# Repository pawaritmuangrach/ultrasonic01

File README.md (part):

# Ultrasonic 40 kHz TDOA — จากต้นแบบ 1 TX + 2 RX สู่ Array แทน LiDAR

หลักการและที่มาของสูตรทั้งหมดอยู่ใน [`US015_TDOA_Codex_Spec.md`](US015_TDOA_Codex_Spec.md) เอกสารนี้สรุปเฉพาะสิ่งที่จำเป็นต่อการต่อวงจร รัน และตีความผลลัพธ์

หัวข้อ 1-6 คือต้นแบบเริ่มต้น (1 TX + 2 RX บน Arduino Nano) ที่ build/upload/ทดสอบจริงแล้ว — ถ้าต้องการภาพรวม
การออกแบบขั้นสูงขึ้น (Y-array, MIMO, ทำไม phased array ใช้ไม่ได้, เปรียบเทียบ Nano/ESP32) ข้ามไปหัวข้อ
**[7. จากต้นแบบ TDOA สู่การออกแบบ Ultrasonic Array เต็มรูปแบบ](#7-จากต้นแบบ-tdoa-สู่การออกแบบ-ultrasonic-array-เต็มรูปแบบ-y-array--mimo)** ได้เลย

## 1. Wiring

```
US-015 board 1 (มีตัวส่ง T และตัวรับ R1)
  VCC  -> 5V
  GND  -> GND
  TRIG -> Nano A2
  ECHO -> Nano A0

US-015 board 2 (ถอด/ปิดหัวส่ง ใช้เฉพาะตัวรับ R2)
  VCC  -> 5V
  GND  -> GND
  TRIG -> Nano A2   (สาย TRIG ต่อร่วมกับบอร์ด 1)
  ECHO -> Nano A1
```

A0/A1/A2 ถูกใช้เป็นขา **digital** ล้วน (PC0/PC1/PC2) ไม่มีการเรียก `analogRead()` กับ ECHO เพราะ ECHO เป็นสัญญาณ LOW/HIGH ไม่ใช่ waveform 40 kHz จริง

### 1.1 กรณีใช้ทรานสดิวเซอร์ดิบ (ไม่มี comparator ในตัว)

ถ้าฮาร์ดแวร์ของคุณเป็นทรานสดิวเซอร์ดิบต่อตรงเข้า A0/A1 (ไม่ใช่โมดูล US-015/HC-SR04 สำเร็จรูปที่มีวงจรขยาย+comparator ในตัว) **จะใช้งานไม่ได้** เพราะสัญญาณจาก piezo รับเป็น AC ระดับ mV เท่านั้น ขา digital input จะไม่เห็น echo จริง ต้องเพิ่มวงจร analog front-end ต่อหน้า A0/A1 แต่ละช่อง ประกอบด้วย 4 สเตจ (ทรานซิสเตอร์ NPN ทั่วไป 4 ตัว/ช่อง):

1. ขยายสัญญาณ 2 สเตจ (common-emitter amplifier, AC-coupled)
2. Envelope detector (ใช้ขา Base-Emitter ของทรานซิสเตอร์อีกตัวแทนไดโอด + ตัวเก็บประจุ)
3. Threshold switch (ทรานซิสเตอร์อีกตัวทำหน้าที่เทียบระดับแทน comparator IC)

วงจรนี้ **output จะ idle ที่ HIGH แล้วลง LOW เมื่อพบสัญญาณ** (กลับด้านกับโมดูลสำเร็จรูป) โค้ดมี flag `ECHO_ACTIVE_LOW` (ตั้งเป็น 1 ไว้แล้วในไฟล์ .ino) เพื่อรองรับ polarity แบบนี้ — ถ้าเปลี่ยนไปใช้โมดูลสำเร็จรูปจริงในอนาคต ให้ตั้งกลับเป็น 0

แนะนำจัดวางแบบสมมาตรสำหรับ calibrate:

```
R1        T        R2
|---------|---------|
      แผ่นสะท้อนเรียบ 30-50 cm ด้านหน้า
```

## 2. Flash และเปิด Serial

1. เปิด `ultrasonic_tdoa_nano/ultrasonic_tdoa_nano.ino` ด้วย Arduino IDE, เลือกบอร์ด "Arduino Nano" / processor ATmega328P (เก่า ถ้า upload ไม่ผ่านให้ลอง "ATmega328P (Old Bootloader)")
2. Upload
3. เปิด Serial Monitor/Serial Plotter ที่ **115200 baud** — หรือใช้หน้าเว็บ simulation ใน `simulation/index.html` แทน (ดูหัวข้อ 6)

ค่าเริ่มต้นของ output คือ **CSV** (ส่ง `s` ทาง Serial เพื่อสลับเป็น human-readable)

Header ของ CSV:

```
timestamp_ms,r1_pulse_us,r2_pulse_us,r1_cm,r2_cm,raw_dt_us,calibrated_dt_us,path_diff_cm,angle_deg,confidence,status,cycle_shift
```

ตัวอย่างบรรทัดข้อมูล:

```
1250,212.5,230.5,3.64,3.95,18.0,18.0,0.617,7.10,91,VALID,0
```

Human-readable (หลังส่ง `s`):

```
R1=212.5us 3.64cm | R2=230.5us 3.95cm | raw_dt=18.0us | calibrated_dt=18.0us | path=0.617cm | angle=7.10deg | confidence=91 | status=VALID | cycle_shift=0
```

## 3. Serial Commands

| คำสั่ง | ผลลัพธ์ |
|---|---|
| `c` | เริ่ม calibration (เก็บ ~200 samples แล้วหา median offset ของ raw dt) — **ต้องวางอุปกรณ์สมมาตรตามรูปด้านบนก่อนส่งคำสั่งนี้** |
| `p` | พิมพ์ parameters ปัจจุบัน (sound speed, spacing, offset, output mode) |
| `r` | ล้าง median-filter / cycle-slip history |
| `s` | สลับ CSV <-> human-readable |
| `t25` | ตั้งอุณหภูมิ 25 °C แล้วคำนวณความเร็วเสียงใหม่ |
| `d5.0` | ตั้ง receiver spacing เป็น 5.0 cm |

## 4. สมการหลัก

```
pulse_us          = fall_tick - rise_tick   (Timer1, 0.5 us/tick)
distance_cm       = pulse_us * c / 2                      (ระยะแบบ pulse-echo ปกติ)
raw_dt_us         = pulse2_us - pulse1_us
calibrated_dt_us  = raw_dt_us - calibration_offset_us      (+ cycle-slip correction)
path_diff_cm      = calibrated_dt_us * c                   (ไม่หาร 2 เพราะเทียบเส้นทางถึงตัวรับสองตัว)
max_dt_us         = receiver_spacing_cm / c                 (ขอบเขตทางฟิสิกส์)
angle_deg         = asin(path_diff_cm / receiver_spacing_cm) * 180/pi   (เฉพาะเมื่อ status == VALID)
```

`c = 0.0343 cm/us` ที่อุณหภูมิห้อง (ปรับได้ด้วยคำสั่ง `t<celsius>`)

## 5. ข้อจำกัดสำคัญ (อ่านก่อนเชื่อผลลัพธ์)

1. US-015 เป็น black-box — ECHO ที่เห็นคือผลหลัง comparator/threshold ภายในโมดูล ไม่ใช่ raw 40 kHz waveform
2. `raw_dt_us` **ไม่รับประกัน** ว่าเท่ากับส่วนต่างเวลาที่คลื่นมาถึงจริง เพราะแต่ละบอร์ดมี internal delay/threshold ไม่เท่ากัน — ต้อง calibrate (`c`) ก่อนเสมอ
3. Calibration ลบ static offset ได้ แต่ลบ dynamic jitter ไม่ได้ทั้งหมด
4. `cycle_shift != 0` แปลว่าเกิด cycle-slip correction (ค่ากระโดดเป็นทวีคูณของ 25 us) — เป็น heuristic ไม่ใช่การพิสูจน์
5. `angle_deg` ใช้สมมติฐาน far-field / plane-wave ถ้าวัตถุอยู่ใกล้มาก มุมนี้จะไม่แม่น
6. ผลลัพธ์ทั้งหมดควรเรียกว่า **pseudo-TDOA** ไม่ใช่ true TDOA จนกว่าจะเข้าถึง raw receiver signal ได้จริง (ดูหัวข้อ 27 ในสเปก)
7. ไม่ควรใช้ระบบนี้ในงาน safety-critical

## 6. Real-time 2D wave simulation

`simulation/index.html` เป็นหน้าเว็บ (self-contained, ไม่ต้องติดตั้งอะไร) ที่:

- ต่อกับ Arduino ผ่าน **Web Serial API** (Chrome/Edge เท่านั้น) ที่ 115200 baud
- อ่านบรรทัด CSV ทีละแถว แล้ววาดภาพ 2D: ตำแหน่ง T/R1/R2, คลื่นวงกลมที่ขยายตัวออกจาก T ไปกระทบวัตถุ (คำนวณตำแหน่งวัตถุจาก r1_cm และระยะ target->R2 ที่แปลงจาก r2_pulse_us) แล้วมีคลื่นสะท้อนกลับไปหา R1 และ R2 พร้อม timing สัมพัทธ์ตามข้อมูลจริง (สโลว์โมชันเพื่อให้ตามองเห็น)
- มีปุ่ม **Demo mode** สำหรับดูตัวอย่างการทำงานโดยไม่ต้องต่อ Arduino จริง
- **สะสมจุดสะท้อนทุกจุดที่ตรวจพบ** (ไม่ใช่แค่ ping ล่าสุด) เป็นแผนที่จุดสีชมพูบานเย็น (magenta point cloud) คล้าย
  scatter plot ของ SLAM map — จุดที่วัดได้ต่อเนื่องกันและอยู่ใกล้กัน (<15 cm) จะมีเส้นเชื่อมให้ดูเป็นขอบวัตถุ/กำแพงคร่าวๆ
  เอาเมาส์ชี้จุดใดก็ได้เพื่อดูระยะ/มุม/confidence ของจุดนั้น มีปุ่ม "Clear Map" และ "Export Map (CSV)"
  หมายเหตุ: เซนเซอร์ชุดนี้ไม่ได้หมุนสแกนแบบ lidar การจะได้แผนที่ห้องเต็มรูปแบบต้องเลื่อน/หมุนวัตถุหรือตัวเซนเซอร์เอง
  แล้วเก็บผลสะสมไว้ (เหมาะกับ Experiment 4 ในสเปก)

วิธีใช้:

1. อัปโหลดโค้ดลง Arduino Nano และปิด Serial Monitor ใน Arduino IDE ก่อน (พอร์ตใช้ได้ทีละโปรแกรม)
2. เปิด `simulation/index.html` ด้วย **Chrome หรือ Edge** (ดับเบิลคลิกเปิดไฟล์ได้เลย ไม่ต้องมี server)
3. กดปุ่ม "Connect Arduino" แล้วเลือกพอร์ต COM ของ Nano
4. ดูคลื่นวิ่งแบบ real-time ทุกครั้งที่ Arduino ยิงคลื่นออกไป

ถ้าต้องการดูตัวอย่างก่อนต่อฮาร์ดแวร์จริง ให้กด "Demo mode (no hardware)" แทน

---

## 7. จากต้นแบบ TDOA สู่การออกแบบ Ultrasonic Array เต็มรูปแบบ (Y-array + MIMO)

หัวข้อ 1-6 ด้านบนคือต้นแบบเริ่มต้น (1 TX + 2 RX, US-015/front-end แบบ discrete transistor) ต่อมาโปรเจกต์ขยายเป้าหมาย
เป็น **ใช้ ultrasonic array แทน LiDAR** สำหรับ obstacle avoidance ระยะใกล้ (เทรน NN โดยใช้กล้องเป็น ground truth)
หัวข้อนี้สรุปข้อค้นพบและการออกแบบที่ได้จากการสำรวจแนวทางต่างๆ

### 7.1 ทำไมตัวส่งหลายตัว + ตัวรับตัวเดียว (phased array) ใช้ไม่ได้

แนวคิดแรกที่พิจารณาคือใช้ตัวส่งหลายตัวรวมคลื่นเป็นลำแคบแล้วกวาดทิศทาง (transmit beam steering) แต่พบข้อจำกัดทาง
ฟิสิกส์ที่แก้ไม่ได้:

- ที่ 40kHz, c=343 m/s → ความยาวคลื่น **λ ≈ 8.575mm** → ต้องวางตัวส่งห่างกันไม่เกิน **λ/2 ≈ 4.3mm** ถึงจะไม่เกิด
  ลำคลื่นหลอก (grating lobe)
- ทรานสดิวเซอร์ TCT40-16 มีตัวถังจริง **16mm** — ใหญ่กว่าที่ต้องการเกือบ 4 เท่า และไม่มีทางวางให้ใกล้กว่านี้ได้
  เพราะเป็นขนาดจริงของอุปกรณ์ในอากาศ
- ทดสอบด้วยการจำลอง (`simulation/beamforming_compare.html`) ยืนยันว่าที่ระยะ 16mm ยิงพร้อมกันเกิดลำคลื่นแรง
  พร้อมกัน **3 ทิศ** (-32°, 0°, 32°) และถ้าพยายาม steer ไป 20° ด้วยการหน่วงเวลา จะยิ่งแย่ลงเป็น **4 ทิศ**
  (-47°, -11°, 20°, 61°)
- **ปัญหานี้แก้ด้วยซอฟต์แวร์ไม่ได้เลย** เพราะพลังงานเสียงกระจายผิดทิศไปแล้วตั้งแต่ในอากาศ ไม่ใช่ความผิดพลาดของ
  การประมวลผลสัญญาณ

สรุป: ตัวส่งหลายตัวยิงพร้อมกันเพื่อเล็งลำคลื่นไม่ใช่ทางที่ไปได้กับทรานสดิวเซอร์ขนาดนี้

### 7.2 ทางที่เลือกแทน: TDOA (วัดเวลา ไม่ใช่วัดเฟส)

แทนที่จะเล็งลำคลื่นตอนส่ง เปลี่ยนมายิงคลื่นกระจายกว้างครั้งเดียว แล้วใช้ **ตัวรับหลายตัว** ฟังพร้อมกัน คำนวณทิศทาง
จากผลต่างเวลาที่เสียงมาถึงแต่ละตัว (`sinθ = c·Δt/d`) สมการนี้มีคำตอบเดียวเสมอ (วัดเวลา ไม่ใช่เฟสที่วนซ้ำทุกคาบ)
จึง**ไม่มี grating lobe** — เป็นเหตุผลที่ต้นแบบในหัวข้อ 1-6 ใช้สถาปัตยกรรมนี้มาตั้งแต่แรก

กฎของ aperture ก็กลับด้านจาก phased array: ความละเอียดเชิงมุม `θ_res ≈ λ/D` → **ยิ่งตัวรับกระจายกว้าง (D ใหญ่)
ยิ่งแยกมุมได้ละเอียด** ตรงข้ามกับ phased array ที่ต้องการให้ชิดกัน

### 7.3 ขยายเพิ่มด้วย MIMO (coded TX หลายตัว)

ยิงตัวส่งหลายตัว**พร้อมกัน**โดยแต่ละตัวใช้ code ต่างกัน (แยกด้วย matched filter ฝั่งรับ) จะได้เส้นทางข้อมูล
(TX→วัตถุ→RX) แยกกันได้ = จำนวน TX × จำนวน RX (virtual array, ตำแหน่งเสมือน = ตำแหน่ง TXi + RXj) — ได้ข้อมูล
เพิ่มแบบ**ทวีคูณ**จากอุปกรณ์ที่เพิ่มแบบบวก และยังยิงครั้งเดียวจบเหมือนเดิม (ไม่ช้าลง เพราะยิงพร้อมกัน) ต่างจาก
การยิงตัวส่งทีละตัว (reciprocity ให้ข้อมูลเท่ากันแต่ช้ากว่า 6 เท่าและวงจรซับซ้อนกว่า จึงไม่คุ้ม)

### 7.4 ผังที่แนะนำ: Scaled Array — 3 TX + 9 RX (12 อุปกรณ์จริง, 27 เส้นทางเสมือน)

- **TX1-TX3**: กลุ่มสามเหลี่ยมเล็กกึ่งกลางแผง (รัศมี 14mm จากศูนย์กลาง — ห่างพอให้ตัวถัง 16mm ไม่ชนกัน)
- **RX1-RX9**: 3 แขนมุม 120° (แบบเดียวกับผัง VLA radio telescope เพื่อ sampling มุมสม่ำเสมอทุกทิศ) แขนละ 3 ตัว
  ที่ระยะ **40 / 80 / 140mm** (140mm คือตัวขยายใหม่จากเดิม 40/80mm)
- แต่ละแขนให้ทั้งข้อมูล azimuth (ซ้าย-ขวา) และ elevation (บน-ล่าง) พร้อมกัน
- Diminishing returns: ขยายรัศมี 40→60mm ได้ θ_res ดีขึ้น 2.05° แต่ขยาย 140→160mm ได้แค่ 0.22° (จึงหยุดที่ 140mm)
- Circuit BOM เต็มระบบ: TX driver (TC4427A) 3 ชุด, MCP6024 (quad op-amp, 2 RX/ชิป) 5 ชิป, วงจร VREF 2.5V 1 ชุด
  (ใช้ร่วมกันได้ทุกช่อง)

### 7.5 ข้อจำกัดของแพลตฟอร์มควบคุม (Nano / ESP32 / ESP32+ADS1115)

| แพลตฟอร์ม | RX สูงสุดที่ใส่ได้จริง | จับ raw chirp 40kHz ได้ไหม | MIMO coded TX |
|---|---|---|---|
| Arduino Nano | ≤6-7 (จาก 8 ขา A0-A7) | ไม่ได้ (ADC มัลติเพล็กซ์ช้าเกิน) → ใช้ envelope+threshold แทน | ไม่ไหว |
| ESP32 เดี่ยว | 8 (ADC1) | ได้ (DMA ~100-500kS/s) | ได้ 3 ตัวเต็มรูปแบบ |
| ESP32 + ADS1115 | 8 + 4 (I2C) | เฉพาะช่อง ESP32; ADS1115 ช้าเกิน (860 SPS) ใช้ได้แค่ envelope | ได้ 3 ตัว |

**สรุป**: ผัง 3TX+9RX เต็มรูปแบบต้องใช้ ESP32+ADS1115 แบบ hybrid (RX 8 ช่องแรกจับ raw waveform ผ่าน ESP32,
RX "far" 140mm ที่เหลือจับแค่ envelope ผ่าน ADS1115) — Nano ทำได้แค่ 1TX+6RX แบบ envelope เท่านั้น

### 7.6 เครื่องมือ visualization ทั้งหมด (self-contained, เปิดตรงจากไฟล์ได้)

| ไฟล์ | ใช้ทำอะไร |
|---|---|
| `simulation/index.html` | Real-time 2D wave + point-cloud map จากข้อมูล serial จริง (หัวข้อ 6) |
| `simulation/beamforming_compare.html` | เปรียบเทียบ interference pattern 2-TX ที่ระยะห่างต่างกัน (λ/2 vs 16mm vs steered) — ที่มาของข้อสรุปข้อ 7.1 |
| `simulation/sparse_array_layout.html` | ผัง L-shape sparse receiver บนโต๊ะ (สำหรับทดลองเก็บข้อมูล + กล้องเป็น ground truth) |
| `simulation/front_array_plate_layout.html` | ผังหน้าแผง Y-array รุ่นแรก (1 TX + 6 RX) พร้อม difference co-array |
| `simulation/mimo_virtual_array_layout.html` | สาธิต MIMO virtual array (3 TX + 4 RX ตัวอย่าง) เทียบกับผัง 1TX+6RX |
| `simulation/scaled_array_layout.html` | ผังสุดท้าย 3TX+9RX เต็มรูปแบบ + diminishing returns + เทียบ 3 แพลตฟอร์ม (7.4-7.5) |
| `diagnostics/r1_basic_test/r1_basic_test.ino` | สเก็ตช์ทดสอบเปล่า (`pulseIn()`) ใช้แยกว่าปัญหา R1 ค้างที่ 4.6cm เป็นที่ฮาร์ดแวร์ ไม่ใช่เฟิร์มแวร์ |

### 7.7 ข้อจำกัดที่ยังเหลืออยู่

**Cycle slip**: คลื่น 40kHz คาบ 25µs ถ้าวัดเวลาไม่แม่นพอ ระบบอาจสับสนว่าจับคลื่นลูกไหน (ค่ากระโดดเป็นก้อนละ ~25µs
— ปรากฏการณ์เดียวกับที่เจอจริงตอน calibrate ฮาร์ดแวร์ในหัวข้อ 2-3) ต่างจาก grating lobe ตรงที่**แก้ได้** ด้วย:

1. Chirp + Pulse Compression (แผนระยะยาว) — กวาดความถี่แทนโทนเดียว ทำให้วัดเวลาคมขึ้นมาก
2. วางตัวรับแบบ sparse/non-redundant — ความกำกวมของแต่ละคู่ตกคนละมุม ไม่ทับกัน
3. Neural Network + กล้องเป็น ground truth — เรียนรู้ล้างส่วนที่เหลือจากข้อมูลจริง

**ข้อจำกัดที่ต้องยอมรับ**: อัลตราโซนิกในอากาศไม่มีวันเทียบ LiDAR ได้ในเรื่องระยะไกล (สิบ-ร้อยเมตร) และความละเอียด
ระดับ mm — เป้าหมายที่สมจริงคือใช้แทนได้เฉพาะบริบท obstacle avoidance ระยะใกล้ (<5-10m) เท่านั้น

---

## 8. ESP32 build log — Stage 1

บันทึกสิ่งที่**วัดได้จริง**บนฮาร์ดแวร์ ไม่ใช่ค่าออกแบบ ทุกตัวเลขในหัวข้อนี้มาจากการวัดด้วย
`esp32_selftest.ino` + `tools/scope_view.py` บนบอร์ด ESP32-D0WD-V3 rev 301 ที่ COM5

### 8.1 สถานะ

| งาน | สถานะ |
|---|---|
| เครื่องมือ (arduino-cli, Python, scope_view) | ✅ |
| พิสูจน์ ADC ต่อเนื่อง 2 MS/s | ✅ |
| ภาคส่ง TX driver Version A | ✅ |
| **ภาครับ RX front-end 1 ช่อง** | ✅ |
| `esp32_scope.ino` (ยิง burst + เก็บคลื่น) | ✅ |
| เห็น echo หลายก้อนในหนึ่งช็อต | ✅ |
| ระยะเลื่อนตาม `t = 2d/c` เมื่อขยับแผ่นสะท้อน | ⬜ |

### 8.2 ADC ต่อเนื่อง — สมมติฐานที่เสี่ยงที่สุดของโปรเจกต์

ทั้งโครงการตั้งอยู่บนข้อสมมติว่า ESP32 สตรีม ADC1 ได้ระดับ MS/s ผลจริง:

| ขอ | ได้จริง | % |
|---|---|---|
| 1,000,000 S/s | 976,400 | 97.6% |
| 1,500,000 S/s | 1,464,200 | 97.6% |
| 2,000,000 S/s | 1,951,900 | 97.6% |

เปอร์เซ็นต์คงที่ทั้งสามค่า แปลว่าเป็น**ค่าโสหุ้ยคงที่ ไม่ใช่เพดาน** — แผน Stage 3
(6 ช่อง × 325 kS/s) จึงใช้ได้จริง

### 8.3 RX front-end — ผลวัดหลังแก้จนนิ่ง

โครงสร้าง: `TCT40-16R → Cin 100nF → 2 สเตจ non-inverting เกน 10.3/สเตจ → R 2.2k + C 1nF → GPIO34`
ไฟเลี้ยง 3.3V, VREF 1.65V จากตัวแบ่ง 10k/10k + บัฟเฟอร์

| ตัวชี้วัด | ค่าที่วัดได้ |
|---|---|
| จุดปฏิบัติการ DC ที่ขาออก | 1.521-1.523 V นิ่งทุกเฟรม |
| ฮัม 50 Hz ที่ขาออก | 3.5 mV |
| พื้นเสียงรบกวน 30-50 kHz | 3.2 mV ที่ขาออก = **30 µV ที่ขาเข้า** |
| จุดอิ่มตัว | 1167 mV rms = 11 mV ที่ขาเข้า |
| ช่วงไดนามิก | **51 dB** |
| ตัวอย่างที่ชนราง (16,000 ตัวอย่าง) | 0 |

> DC 1.52 V ไม่ใช่ความผิดพลาด — ADC ของ ESP32 อ่านต่ำกว่าจริงราว 7% ที่ช่วงกลางสเกล
> `1.65 × 0.923 = 1.523` ตรงกับที่วัดได้ ต้องคาลิเบรตก่อนใช้ค่าสัมบูรณ์

**ทดสอบตอบสนองอัลตราโซนิก** (เขย่าพวงกุญแจห่าง ~10 cm):

| | พลังงานย่าน 30-50 kHz |
|---|---|
| ห้องเงียบ | 3.2 mV |
| เขย่ากุญแจ | 337.4 mV (**105 เท่า**) |

หลักฐานที่หนักแน่นกว่าความแรงคือ**ความถี่**: กุญแจให้เสียงกว้าง แต่ยอดที่จับได้ทุกเฟรมตกอยู่ที่
36.07 / 37.31 / 37.33 / 37.35 / 38.00 / 38.04 / 38.07 / 40.70 kHz — เกาะกลุ่มในย่านเรโซแนนซ์
ของ TCT40 ทั้งหมด ถ้าเป็นเพียงสัญญาณรบกวน ยอดจะกระจายแบบสุ่มทั่วย่าน

### 8.4 ปัญหาที่เจอจริงและวิธีวินิจฉัย

บันทึกไว้เพราะทั้งสี่ข้อจะกลับมาอีกตอนขยายเป็น 6 ช่อง

| อาการ | สาเหตุจริง | วิธีที่ชี้ตัวได้ |
|---|---|---|
| ขาออกแกว่งเต็มราง 3.3 Vpp ที่ 50 Hz | **รางไฟบนบอร์ดทดลองถูกตัดขาดกลางแผ่น** ครึ่งล่าง (ตัวแบ่ง VREF, C 10µF, Cg, C_out, คาปาบายพาส) ไม่มีทั้งไฟและกราวด์ กลายเป็นเสาอากาศรับไฟบ้าน แล้ว C 10µF ป้อนเข้า VREF ตรงๆ | ย้ายสายวัดไปที่รางกราวด์เอง — อ่านได้ 0.556 V แกว่ง 3.3 Vpp ซึ่งเป็นไปไม่ได้ถ้าต่อถึงกราวด์จริง |
| แยกไม่ออกว่าวงจรเสียหรือสายวัดลอย | — | อ่านขาที่**ไม่ได้ต่ออะไรเลย** (GPIO36/39) เทียบ ได้ 22 mV เทียบกับ 2093 mV จึงยืนยันว่าวงจรสร้างสัญญาณจริง |
| ไม่รู้ว่าเป็นการแกว่งเองหรือรับจากภายนอก | ฮัมจากภายนอก | ดูค่าดิบ: 98.5% ของตัวอย่างเป็น 0 หรือ 4095 เป๊ะ ฮาร์มอนิก 49/146/244/342 Hz อัตราส่วน 1 : ⅓ : ⅕ : ⅐ = คลื่นสี่เหลี่ยมที่ถูกตัดยอด ไม่ใช่การแกว่งของ op-amp |
| ออปแอมป์ตัวที่ 4 ที่ไม่ได้ใช้ | ขา 12 (ขาออก) ต่อลงกราวด์ = ลัดวงจร ส่วนขา 13/14 ลอย | อินพุต CMOS ที่ลอยจะทำตัวเป็นตัวเปรียบเทียบรับไฟบ้าน — **ออปแอมป์ที่ไม่ได้ใช้ต้องต่อเป็นวงจรตามแรงดัน**: ขาออก↔อินพุต− และอินพุต+ ลงกราวด์ |

**บทเรียนที่ใช้ซ้ำได้**: ตอนที่ `Cg` เปลี่ยนเป็น 1nF เกนที่ 50 Hz เหลือ 1.03/สเตจ ทำให้ขาออกของ
สเตจ 1 กับสเตจ 2 ให้ค่า**เท่ากันเป๊ะทุกหลัก** (2093.5 กับ 2093.7 mV) ทั้งที่สเตจ 2 ควรขยาย
สเตจ 1 อีก 10 เท่า — ความผิดปกตินี้เองที่ชี้ว่าปัญหาอยู่**เหนือ**ทางขยายขึ้นไป คือที่ VREF
การเปลี่ยนอะไหล่ครั้งนั้นไม่ได้แค่แก้ฮัม แต่เปลี่ยนวงจรให้กลายเป็นเครื่องมือวินิจฉัยด้วย

### 8.5 คำสั่งที่ใช้วัดซ้ำได้

```bash
python tools/scope_view.py --port COM5 --dc --probe 34 --rate 200000 --samples 8000
```

### 8.6 ผลยิงจริงครั้งแรก — ภาคส่ง + ภาครับ ครบวงจร

เฟิร์มแวร์ `esp32_array/esp32_scope/esp32_scope.ino` ยิง burst 8 รอบที่ 40 kHz ออก GPIO25
แล้วเก็บคลื่นจาก GPIO34 ที่ 500 kS/s หน้าต่าง 48 ms (= ระยะ 8.2 m)

**หนึ่งช็อตเห็นวัตถุ 8 ก้อน** (แปลงเป็นระยะจากผลต่างกับพัลส์ตรง):

| t (ms) | ห่างจากพัลส์ตรง | ระยะ | ยอด |
|---|---|---|---|
| 1.436 | — | พัลส์ตรง (t=0) | 49.0 mV |
| 3.789 | 2.352 ms | 40.3 cm | 74.3 mV |
| 4.394 | 2.957 ms | 50.7 cm | 26.0 mV |
| 6.155 | 4.718 ms | 80.9 cm | 81.9 mV |
| 7.709 | 6.273 ms | 107.6 cm | 35.8 mV |
| 8.300 | 6.864 ms | 117.7 cm | 41.9 mV |
| 8.925 | 7.489 ms | 128.4 cm | 29.3 mV |

**ความถี่พาหะที่วัดได้** (พารามิเตอร์บิน 61 Hz จากการประมาณค่าพาราโบลา): พัลส์ตรง 40.94 kHz,
เอคโค่ 41.03 / 41.83 kHz — อยู่ในกรอบ 40 ±1 kHz ตามเกณฑ์ และบอกด้วยว่า**เรโซแนนซ์จริงของคู่
ทรานสดิวเซอร์นี้อยู่ที่ ~41 kHz ไม่ใช่ 40 kHz พอดี** ลองสั่ง `s 41000` ดูอาจได้แรงขึ้นฟรีๆ

**SNR ของเอคโค่ที่ 40 cm = 29.5 dB** (พื้นหลัง 2.82 mV) เกณฑ์ Stage 1 ต้องการ ≥10 dB ที่ 50 cm

### 8.7 ทำไม t = 0 ต้องอ่านจากพัลส์ตรง ไม่ใช่จากเวลาที่ซอฟต์แวร์สั่งยิง

ยิงซ้ำ 8 ครั้งติดกัน วัดเวลามาถึงของพัลส์ตรง (ระยะทางคงที่ ไม่ควรขยับเลย):

| | ค่า |
|---|---|
| ตำแหน่งที่เฟิร์มแวร์ตั้งใจให้ยิง (`p 200`) | 0.200 ms |
| ตำแหน่งจริงเฉลี่ย | **1.454 ms** |
| ความคลาดเคลื่อนคงที่ | **1.25 ms = ระยะผิด 21 cm** |
| การกระจายรอบค่าเฉลี่ย | 24.3 µs (ช่วง 74 µs) |

ความคลาดเคลื่อนคงที่ 1.25 ms เกิดจาก DMA ของ ADC วิ่งอิสระ — ตอนที่เฟิร์มแวร์ล้างบัฟเฟอร์แล้ว
เริ่มนับ ตัวอย่างแรกที่ได้จริงไม่ได้เกิดขึ้น ณ วินาทีนั้น **ถ้าเชื่อเวลาของซอฟต์แวร์ ทุกระยะจะเพี้ยนไป
21 cm** แต่พอวัดเทียบกับพัลส์ตรงในข้อมูลเอง ความคลาดเคลื่อนนี้หักล้างหมดเกลี้ยง เพราะมันเข้าไป
อยู่ในทั้งสองพจน์เท่ากัน

วัดระยะซ้ำ 8 ครั้งกับวัตถุเดียวกันได้ **40.6 cm ± 7.3 mm**

> ข้อสังเกตที่สำคัญต่อ Stage 2: การกระจายของ**ผลต่าง** (42.4 µs) แย่กว่าการกระจายของ
> **เวลาสัมบูรณ์ของเอคโค่** (37.5 µs) ทั้งที่การลบควรหักสิ่งที่ร่วมกันออก แปลว่าตัวจำกัดความแม่น
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
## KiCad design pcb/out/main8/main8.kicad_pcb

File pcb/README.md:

# pcb — ข้อมูลและลายสำหรับสั่งทำ PCB

ทั้ง TX และ RX สร้างจากวงจรที่ **ต่อบนแผ่นไข่ปลาแล้วใช้งานได้จริง**
ไม่ได้ออกแบบวงจรใหม่ ที่มา: [`../hardware/rx_frontend.md`](../hardware/rx_frontend.md) ·
[`../hardware/tx_driver.md`](../hardware/tx_driver.md) และผังไข่ปลาใน `../hardware/diagrams/`

```bash
python pcb/build.py       # สร้างไฟล์ทั้งหมดใหม่
python pcb/check_out.py   # ตรวจไฟล์ที่จะส่งโรงงาน
```

---

## บอร์ดทั้งสาม

| บอร์ด | ขนาด | ทำอะไร | สั่งกี่แผ่น |
|---|---|---|---|
| **`tx3`** | 66.8 × 38.3 mm | ภาคส่ง 3 หัว จาก 74HCT04 ตัวเดียว | 1 |
| **`rx2`** | 86.8 × 73.8 mm | ภาครับ 2 ช่อง จาก MCP6004 ตัวเดียว | **5** (ได้ 10 ช่อง ใช้ 9) |
| **`vref`** | 68.8 × 51.9 mm | สร้าง 1.65V ครั้งเดียว แจกทุกบอร์ด | 1 |

### ทำไมแยก VREF ออกมาเป็นบอร์ดที่สาม

MCP6004 มี 4 section พอดีกับ 2 ช่องรับ (ช่องละ 2 สเตจ) **ไม่เหลือให้ทำบัฟเฟอร์ VREF**
ผังไข่ปลาเดิมแก้ด้วยการให้ชิปแรกทำแค่ 1 ช่อง แล้วเอา section ที่เหลือไปทำ VREF
ซึ่งทำให้บอร์ดสองแบบไม่เหมือนกัน สั่งทำแล้วยุ่ง

แยกออกมาได้บอร์ดรับที่ **เหมือนกันทุกแผ่น ปั๊มซ้ำได้** และได้ผลพลอยได้ที่สำคัญกว่า:
VREF เป็นจุดเดียวกันจริงทั้งระบบ ถ้าแต่ละบอร์ดสร้างเอง ค่าจะต่างกันตามความคลาด
ของตัวต้านทาน แล้วช่องต่าง ๆ จะมีจุดศูนย์ไม่ตรงกัน — เวลาเทียบความแรงระหว่างช่อง
(ซึ่งคือที่มาของมุม) จะเพี้ยน

---

## ไฟล์ในแต่ละโฟลเดอร์ `out/<บอร์ด>/`

| ไฟล์ | คืออะไร |
|---|---|
| `*-F_Cu.gbr` `*-B_Cu.gbr` | ลายทองแดงด้านบน / ด้านล่าง |
| `*-F_Mask.gbr` `*-B_Mask.gbr` | หน้ากากประสาน (เปิดเฉพาะตรงแป้น) |
| `*-F_Silkscreen.gbr` | ตัวหนังสือและกรอบชิ้นส่วนด้านบน |
| `*-Edge_Cuts.gbr` | เส้นตัดขอบบอร์ด |
| `*.drl` | ตำแหน่งและขนาดรูเจาะ |
| `preview.png` | ภาพตรวจด้วยตา — ม่วง/เขียวเข้ม = แผ่นกราวด์ · เขียวสด = ลายด้านล่าง |
| `assembly.png` | **ผังลงชิ้นส่วน ถือไว้ตอนบัดกรี** |
| `BOM.md` | รายการชิ้นส่วนของบอร์ดนั้น |
| `nets.md` | ตารางว่าขาไหนต้องปี๊บถึงขาไหน ไว้ไล่วัดด้วยมิเตอร์ |

---

## สั่งทำยังไง

zip ไฟล์ `.gbr` กับ `.drl` ของบอร์ดหนึ่งรวมกัน แล้วอัปโหลดที่ JLCPCB / PCBWay / Elecrow

ตั้งค่า: **2 ชั้น · หนา 1.6 mm · ทองแดง 1 oz** — ค่าเริ่มต้นของทุกเจ้าใช้ได้หมด
ไม่มีอะไรพิเศษ ราคาปกติ 5 แผ่นแรกไม่กี่สิบบาท

**ก่อนจ่ายเงิน ให้เปิดดูในตัวดู Gerber ของเว็บนั้นก่อนเสมอ** แล้วเทียบกับ `preview.png`
ถ้าสองภาพไม่เหมือนกัน อย่าสั่ง

### กติกาที่ใช้ออกแบบ (เผื่อไว้เยอะกว่าที่โรงงานทำได้)

| | ค่าที่ใช้ | โรงงานทั่วไปทำได้ |
|---|---|---|
| ลายสัญญาณ | 0.4 mm | 0.13 mm |
| ลายไฟ | 0.8 mm | |
| ระยะห่างขั้นต่ำ | 0.4 mm | 0.13 mm |
| รูเล็กสุด | 0.9 mm | 0.3 mm |
| ทองแดงรอบรู | 0.4 mm | 0.13 mm |

เผื่อเยอะขนาดนี้เพราะสองเหตุผล: สั่งเจ้าไหนก็ผ่านแน่ และถ้าจะกัดเองที่บ้านก็ยังทำได้

---

## ถ้าจะทำเอง (รีดลายลงแผ่นทองแดง)

`tx3` และ `vref` เดินลายอยู่ **ด้านล่างล้วน** (ลายด้านบน 0 เส้น) ทำหน้าเดียวได้เลย
`rx2` มีลายด้านบน 6 เส้น ต้องแทนด้วยสายจัมป์ 6 เส้นบนด้านชิ้นส่วน

พิมพ์ `*-B_Cu.gbr` แบบ **กลับซ้ายขวา** ที่ 1:1 (เปิดด้วย gerbv หรือ KiCad ฟรี)
ข้อแลกเปลี่ยน: ทำเองจะไม่มีแผ่นกราวด์ด้านบน ซึ่งเป็นตัวที่ช่วยเรื่อง noise มากที่สุด

---

## แผ่นกราวด์ — จุดที่ตั้งใจทำเป็นพิเศษ

กราวด์ไม่ได้ลากเป็นเส้น แต่**เททองแดงเต็มทั้งสองด้าน**

วงจรรับขยาย 34 เท่าสองสเตจ = **1,156 เท่า** กระแสกลับของช่องหนึ่งที่วิ่งผ่าน
ลายกราวด์ยาว ๆ จะสร้างแรงดันตกคร่อมที่ช่องอื่นอ่านเป็นสัญญาณ = ครอสทอล์ก
แผ่นกราวด์ให้กระแสกลับวิ่งใต้ลายสัญญาณตรง ๆ วงจึงเล็กที่สุดเท่าที่เป็นไปได้

โปรเจกต์นี้เคยวัดแล้วว่า**เพิ่มสายกราวด์สั้นเส้นเดียวลด noise ได้ 3.3 เท่า** —
นี่คือเหตุผลที่ยอมออกแบบให้ยากขึ้นเพื่อได้แผ่นกราวด์

รอบขากราวด์ทุกขาเว้น **คูกันความร้อน** เหลือซี่เชื่อมสี่ทิศ ถ้าเชื่อมเต็มหน้า
แผ่นทองแดงจะดูดความร้อนจนหัวแร้งธรรมดาบัดกรีขาไม่ติด

---

## การต่อระหว่างบอร์ด

```
        ESP32                      vref
     GPIO18/19/21 ──┐         ┌── 3V3 ──┐
          GND ──────┼─→ tx3   │         ├─→ rx2 (5 แผ่น) J1: 3V3 · GND · VREF
                    │         └── GND ──┘
        +5V ────────┴─→ tx3 JP          rx2 J2: OUT1 · OUT2 · GND ─→ ADC ของ ESP32
```

**ห้ามต่อขาออกของ 74HCT04 (5V) กลับเข้า GPIO ของ ESP32** — พังถาวร ทิศทางมีทางเดียว
ESP32 (3.3V) → อินพุตชิป เท่านั้น

ขา ADC ที่ใช้ได้มีแค่ **ADC1**: GPIO 32, 33, 34, 35, 36, 39 (6 ขา)
ครบ 9 ช่องต้องมัลติเพล็กซ์หรือเพิ่ม ADC ภายนอก — **ยังไม่ได้แก้ในบอร์ดชุดนี้**

---

## วิธีตรวจ

มีตัวตรวจสองชั้น คนละหน้าที่ เพราะพลาดกันคนละแบบ:

1. **`router.verify`** ดู *ลายที่คิดได้* — ขาของเน็ตเดียวกันต่อถึงกันจริงไหม
   และทองแดงคนละเน็ตเข้าใกล้กันเกิน 0.4 mm ไหม โดยอ่านจากทองแดงที่ได้จริง
   ไม่ใช่จากที่ตั้งใจเดิน

2. **`check_out.py`** ดู *ไฟล์ที่จะส่งโรงงาน* — ครบไฟล์ไหม ไวยากรณ์ถูกไหม
   ของอยู่ในขอบบอร์ดไหม

ชั้นที่สองไม่ใช่ของเกิน — **เคยพลาดจริง** ตอนแรกแผ่นกราวด์ถูกต้องในหน่วยความจำ
และตัวตรวจชั้นแรกบอกว่าผ่าน แต่ยังไม่ได้เขียนลงไฟล์ Gerber เลย
บอร์ดที่ผลิตจะไม่มีกราวด์ทั้งที่ทุกอย่าง "ผ่าน"

---

## ข้อจำกัดที่ต้องรู้ก่อนสั่ง

- **ยังไม่เคยผลิตจริง** ไฟล์ผ่านตัวตรวจที่ผมเขียนเอง ยังไม่เคยผ่านโรงงาน
  หรือโปรแกรมดู Gerber ของคนอื่น **เปิดดูในเว็บโรงงานก่อนจ่ายเงินเสมอ**
- **ระยะขาชิ้นส่วนเป็นค่ามาตรฐาน ไม่ได้วัดจากของจริงที่คุณมี**
  โดยเฉพาะคาปาอิเล็กโทรไลต์ 10µF (ใช้ 2.54 mm) และหัวต่อทรานสดิวเซอร์
  ควรวัดของจริงเทียบก่อน
- **ไม่มีผังวงจรแบบรูปวาด** ในโฟลเดอร์นี้ — ผังวงจรอยู่ที่ `hardware/rx_frontend.md`
  และ `hardware/tx_driver.md` ส่วนที่นี่มี `nets.md` (ตารางการต่อ ตรงไปตรงมากว่า)
  กับ `assembly.png` (ผังลงชิ้นส่วน)
- **หัวรับ/หัวส่งต่อผ่านหัวต่อ 2 ขา** ไม่ได้บัดกรีลงบอร์ดตรง ๆ
  เพราะทรานสดิวเซอร์ต้องไปติดบนแผ่นหน้า (`plate_mini`) ไม่ได้อยู่บนบอร์ด
- **ยังไม่แก้เรื่อง ADC ไม่พอ** — ESP32 มี ADC1 แค่ 6 ขา แต่แผนคือ 9 ช่องรับ

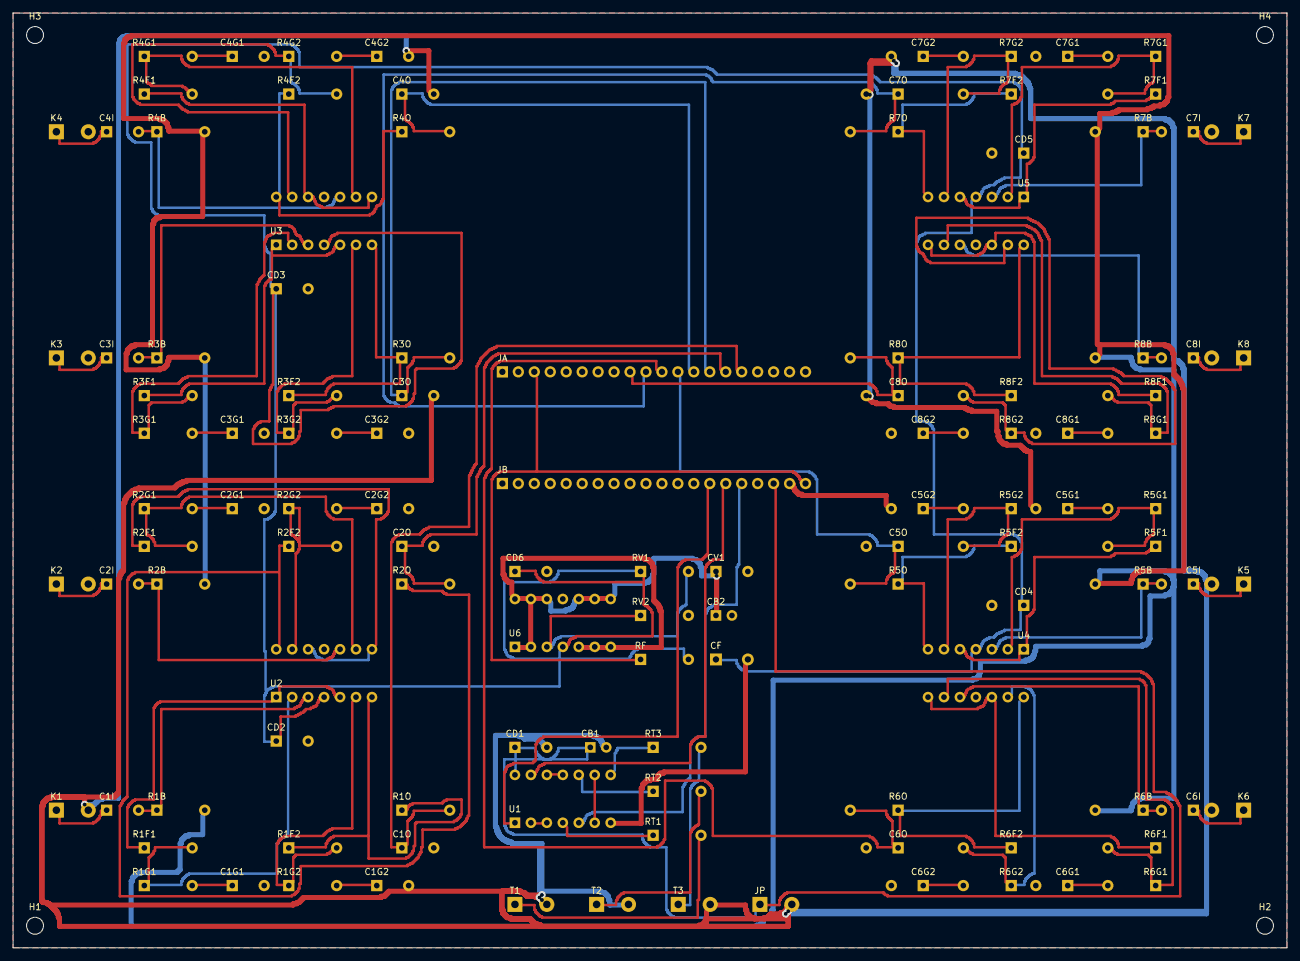
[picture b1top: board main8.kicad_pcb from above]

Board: 2 copper layers, 202.8 x 148.8 mm, 120 parts (0 on the bottom side), 90 nets.

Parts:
C1G1, C1G2, C2G1, C2G2, C3G1, C3G2, C4G1, C4G2, C5G1, C5G2, C6G1, C6G2, C7G1, C7G2, C8G1, C8G2: 100nF; C_DISC
C1I, C2I, C3I, C4I, C5I, C6I, C7I, C8I: 10nF; C_DISC
C1O, C2O, C3O, C4O, C5O, C6O, C7O, C8O: 1nF; C_DISC
CB1, CB2: 10uF; C_ELEC
CD1, CD2, CD3, CD4, CD5, CD6: 100nF; C_DISC
CF: 100uF; C_BULK
CV1: 100nF; C_DISC
H1, H2, H3, H4: M2.5; MountingHole
JA: Blue Pill; HDR20
JB: Blue Pill; HDR20
JP: 5V IN; TERM2
K1: RX1; TERM2
K2: RX2; TERM2
K3: RX3; TERM2
K4: RX4; TERM2
K5: RX5; TERM2
K6: RX6; TERM2
K7: RX7; TERM2
K8: RX8; TERM2
R1B, R2B, R3B, R4B, R5B, R6B, R7B, R8B: 1M; R_AXIAL
R1F1, R1F2, R2F1, R2F2, R3F1, R3F2, R4F1, R4F2, R5F1, R5F2, R6F1, R6F2, R7F1, R7F2, R8F1, R8F2: 33k; R_AXIAL
R1G1, R1G2, R1O, R2G1, R2G2, R2O, R3G1, R3G2, R3O, R4G1, R4G2, R4O, R5G1, R5G2, R5O, R6G1, R6G2, R6O, R7G1, R7G2, R7O, R8G1, R8G2, R8O: 1k; R_AXIAL
RF: 10R; R_AXIAL
RT1, RT2, RT3: 100R; R_AXIAL
RV1, RV2: 10k; R_AXIAL
T1: TX1; TERM2
T2: TX2; TERM2
T3: TX3; TERM2
U1: 74HCT04; DIP14
U2, U3, U4, U5, U6: MCP6024; DIP14

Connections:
A3V3: CD2.1, CD3.1, CD4.1, CD5.1, CD6.1, CF.1, RF.2, RV1.1, U2.4, U3.4, U4.4, U5.4, U6.4
GND: C1G1.2, C1G2.2, C1O.2, C2G1.2, C2G2.2, C2O.2, C3G1.2, C3G2.2, C3O.2, C4G1.2, C4G2.2, C4O.2, C5G1.2, C5G2.2, C5O.2, C6G1.2, C6G2.2, C6O.2, C7G1.2, C7G2.2, C7O.2, C8G1.2, C8G2.2, C8O.2, CB1.2, CB2.2, CD1.2, CD2.2, CD3.2, CD4.2, CD5.2, CD6.2, CF.2, CV1.2, JA.1, JA.2, JB.19, JP.2, K1.2, K2.2, K3.2, K4.2, K5.2, K6.2, K7.2, K8.2, RV2.2, T1.2, T2.2, T3.2, U1.7, U2.11, U3.11, U4.11, U5.11, U6.11
MCU3V3: JA.3, JB.20, RF.1
MID: RV1.2, RV2.1, U6.3
P5V: CB1.1, CD1.1, JB.18, JP.1, U1.14
RX1_ADC: C1O.1, JA.16, R1O.2
RX1_G: C1I.2, R1B.1, U2.3
RX1_G1: C1G1.1, R1G1.2
RX1_G2: C1G2.1, R1G2.2
RX1_IN: C1I.1, K1.1
RX1_S1N: R1F1.2, R1G1.1, U2.2
RX1_S1O: R1F1.1, U2.1, U2.5
RX1_S2N: R1F2.2, R1G2.1, U2.6
RX1_S2O: R1F2.1, R1O.1, U2.7
RX2_ADC: C2O.1, JA.15, R2O.2
RX2_G: C2I.2, R2B.1, U2.10
RX2_G1: C2G1.1, R2G1.2
RX2_G2: C2G2.1, R2G2.2
RX2_IN: C2I.1, K2.1
RX2_S1N: R2F1.2, R2G1.1, U2.9
RX2_S1O: R2F1.1, U2.8, U2.12
RX2_S2N: R2F2.2, R2G2.1, U2.13
RX2_S2O: R2F2.1, R2O.1, U2.14
RX3_ADC: C3O.1, JA.14, R3O.2
RX3_G: C3I.2, R3B.1, U3.3
RX3_G1: C3G1.1, R3G1.2
RX3_G2: C3G2.1, R3G2.2
RX3_IN: C3I.1, K3.1
RX3_S1N: R3F1.2, R3G1.1, U3.2
RX3_S1O: R3F1.1, U3.1, U3.5
RX3_S2N: R3F2.2, R3G2.1, U3.6
RX3_S2O: R3F2.1, R3O.1, U3.7
RX4_ADC: C4O.1, JA.13, R4O.2
RX4_G: C4I.2, R4B.1, U3.10
RX4_G1: C4G1.1, R4G1.2
RX4_G2: C4G2.1, R4G2.2
RX4_IN: C4I.1, K4.1
RX4_S1N: R4F1.2, R4G1.1, U3.9
RX4_S1O: R4F1.1, U3.8, U3.12
RX4_S2N: R4F2.2, R4G2.1, U3.13
RX4_S2O: R4F2.1, R4O.1, U3.14
RX5_ADC: C5O.1, JA.12, R5O.2
RX5_G: C5I.2, R5B.1, U4.3
RX5_G1: C5G1.1, R5G1.2
RX5_G2: C5G2.1, R5G2.2
RX5_IN: C5I.1, K5.1
RX5_S1N: R5F1.2, R5G1.1, U4.2
RX5_S1O: R5F1.1, U4.1, U4.5
RX5_S2N: R5F2.2, R5G2.1, U4.6
RX5_S2O: R5F2.1, R5O.1, U4.7
RX6_ADC: C6O.1, JA.11, R6O.2
RX6_G: C6I.2, R6B.1, U4.10
RX6_G1: C6G1.1, R6G1.2
RX6_G2: C6G2.1, R6G2.2
RX6_IN: C6I.1, K6.1
RX6_S1N: R6F1.2, R6G1.1, U4.9
RX6_S1O: R6F1.1, U4.8, U4.12
RX6_S2N: R6F2.2, R6G2.1, U4.13
RX6_S2O: R6F2.1, R6O.1, U4.14
RX7_ADC: C7O.1, JA.10, R7O.2
RX7_G: C7I.2, R7B.1, U5.3
RX7_G1: C7G1.1, R7G1.2
RX7_G2: C7G2.1, R7G2.2
RX7_IN: C7I.1, K7.1
RX7_S1N: R7F1.2, R7G1.1, U5.2
RX7_S1O: R7F1.1, U5.1, U5.5
RX7_S2N: R7F2.2, R7G2.1, U5.6
RX7_S2O: R7F2.1, R7O.1, U5.7
RX8_ADC: C8O.1, JA.9, R8O.2
RX8_G: C8I.2, R8B.1, U5.10
RX8_G1: C8G1.1, R8G1.2
RX8_G2: C8G2.1, R8G2.2
RX8_IN: C8I.1, K8.1
RX8_S1N: R8F1.2, R8G1.1, U5.9
RX8_S1O: R8F1.1, U5.8, U5.12
RX8_S2N: R8F2.2, R8G2.1, U5.13
RX8_S2O: R8F2.1, R8O.1, U5.14
TX1_DRV: RT1.2, T1.1
TX1_IN: JB.14, U1.1
TX1_MID: U1.2, U1.3
TX1_OUT: RT1.1, U1.4
TX2_DRV: RT2.2, T2.1
TX2_IN: JB.15, U1.13
TX2_MID: U1.11, U1.12
TX2_OUT: RT2.1, U1.10
TX3_DRV: RT3.2, T3.1
TX3_IN: JB.16, U1.5
TX3_MID: U1.6, U1.9
TX3_OUT: RT3.1, U1.8
VREF: CB2.1, CV1.1, R1B.2, R2B.2, R3B.2, R4B.2, R5B.2, R6B.2, R7B.2, R8B.2, U6.1, U6.2, U6.5, U6.6, U6.7, U6.8, U6.9, U6.10, U6.12, U6.13, U6.14

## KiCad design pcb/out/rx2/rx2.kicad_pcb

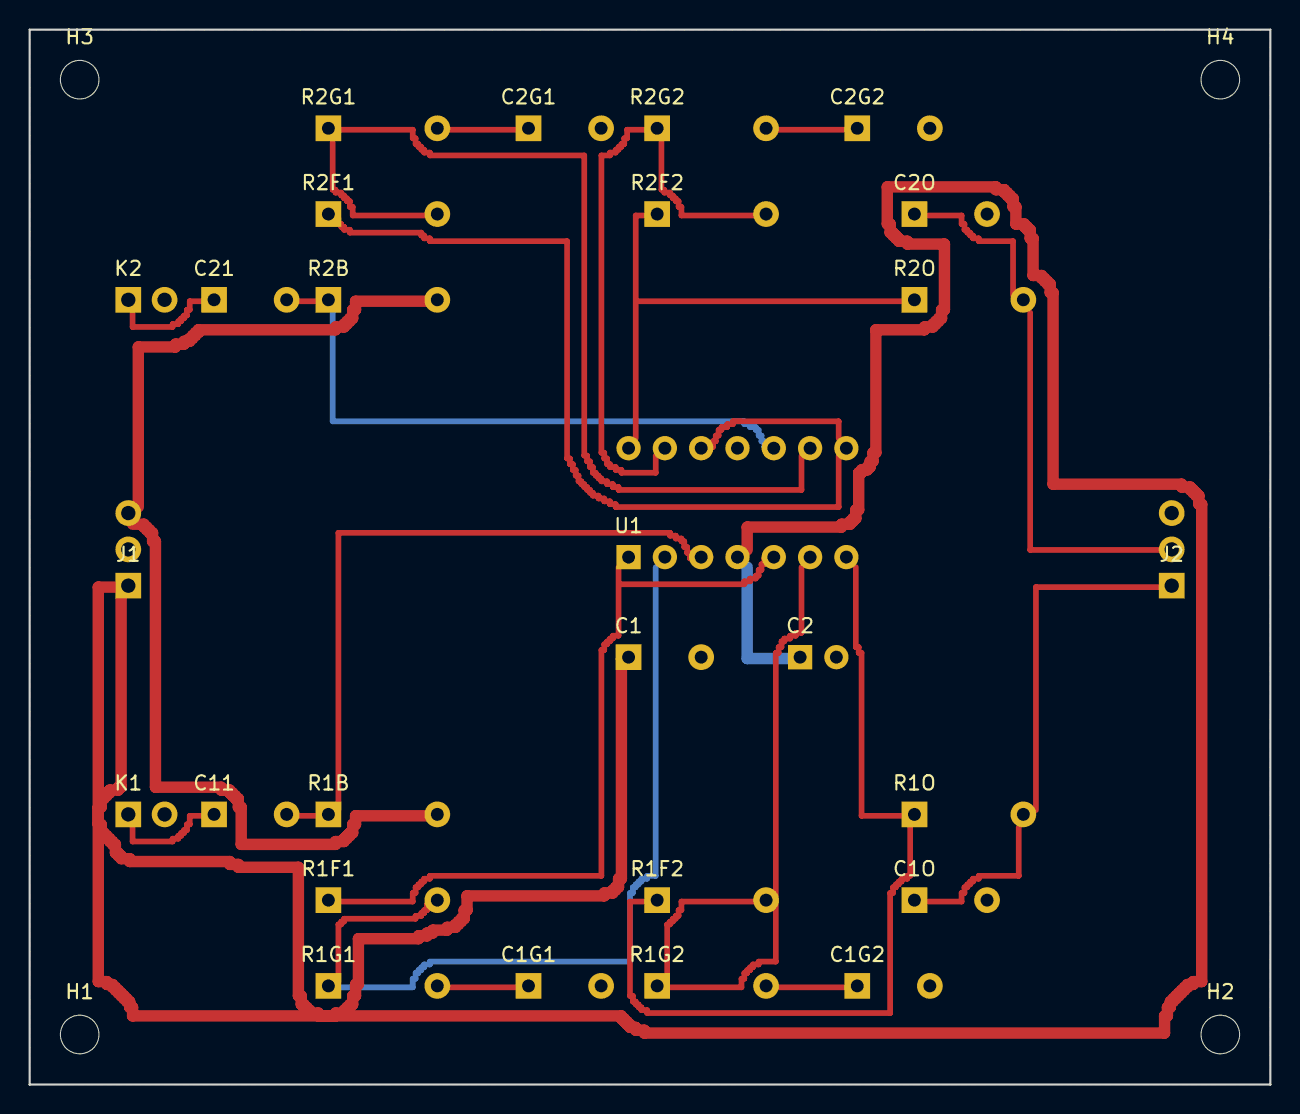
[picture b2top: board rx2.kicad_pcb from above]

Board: 2 copper layers, 86.8 x 73.8 mm, 31 parts (0 on the bottom side), 21 nets.

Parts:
C1, C1G1, C1G2, C2G1, C2G2: 100nF; C_DISC
C1O, C2O: 1nF; C_DISC
C2: 10uF; C_ELEC
C11, C21: 10nF; C_DISC
H1, H2, H3, H4: M2.5; MountingHole
J1: PWR+VREF; HDR3
J2: ADC OUT; HDR3
K1, K2: TCT40-16R; HDR2
R1B, R2B: 1M; R_AXIAL
R1F1, R1F2, R2F1, R2F2: 33k; R_AXIAL
R1G1, R1G2, R1O, R2G1, R2G2, R2O: 1k; R_AXIAL
U1: MCP6004; DIP14

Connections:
3V3: C1.1, C2.1, J1.1, U1.4
CH1_G: C11.2, R1B.1, U1.3
CH1_G1: C1G1.1, R1G1.2
CH1_G2: C1G2.1, R1G2.2
CH1_IN: C11.1, K1.1
CH1_OUT: C1O.1, J2.1, R1O.2
CH1_S1N: R1F1.2, R1G1.1, U1.2
CH1_S1O: R1F1.1, U1.1, U1.5
CH1_S2N: R1F2.2, R1G2.1, U1.6
CH1_S2O: R1F2.1, R1O.1, U1.7
CH2_G: C21.2, R2B.1, U1.10
CH2_G1: C2G1.1, R2G1.2
CH2_G2: C2G2.1, R2G2.2
CH2_IN: C21.1, K2.1
CH2_OUT: C2O.1, J2.2, R2O.2
CH2_S1N: R2F1.2, R2G1.1, U1.9
CH2_S1O: R2F1.1, U1.8, U1.12
CH2_S2N: R2F2.2, R2G2.1, U1.13
CH2_S2O: R2F2.1, R2O.1, U1.14
GND: C1.2, C1G1.2, C1G2.2, C1O.2, C2.2, C2G1.2, C2G2.2, C2O.2, J1.2, J2.3, K1.2, K2.2, U1.11
VREF: J1.3, R1B.2, R2B.2

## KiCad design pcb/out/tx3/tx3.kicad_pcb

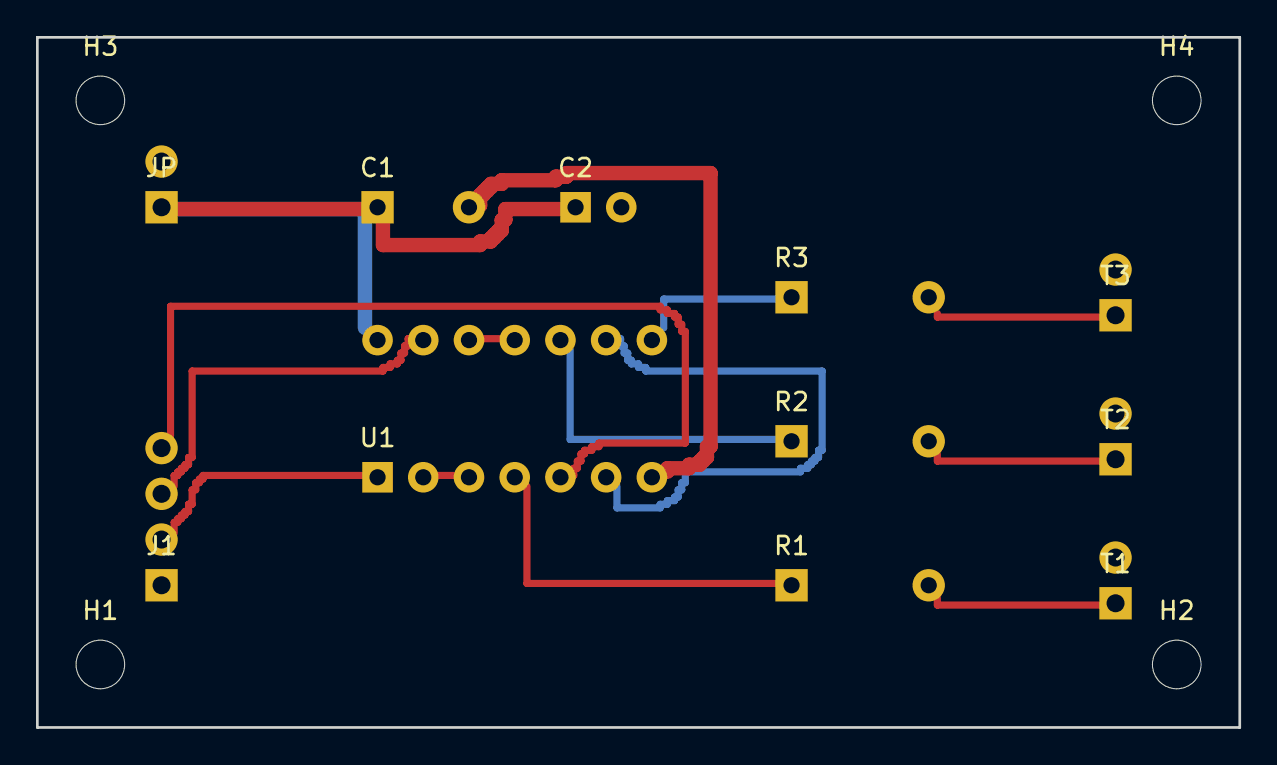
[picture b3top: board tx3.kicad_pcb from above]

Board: 2 copper layers, 66.8 x 38.3 mm, 15 parts (0 on the bottom side), 14 nets.

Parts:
C1: 100nF; C_DISC
C2: 10uF; C_ELEC
H1, H2, H3, H4: M2.5; MountingHole
J1: ESP32; HDR4
JP: PWR; HDR2
R1, R2, R3: 100R; R_AXIAL
T1, T2, T3: TCT40-16T; HDR2
U1: 74HCT04; DIP14

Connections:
+5V: C1.1, C2.1, JP.1, U1.14
GND: C1.2, C2.2, J1.1, JP.2, T1.2, T2.2, T3.2, U1.7
TX1_DRV: R1.2, T1.1
TX1_IN: J1.2, U1.1
TX1_MID: U1.2, U1.3
TX1_OUT: R1.1, U1.4
TX2_DRV: R2.2, T2.1
TX2_IN: J1.3, U1.13
TX2_MID: U1.11, U1.12
TX2_OUT: R2.1, U1.10
TX3_DRV: R3.2, T3.1
TX3_IN: J1.4, U1.5
TX3_MID: U1.6, U1.9
TX3_OUT: R3.1, U1.8

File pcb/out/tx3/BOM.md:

# tx3 — รายการชิ้นส่วน



| ค่า | ตัวถัง | จำนวน | อ้างอิง |
|---|---|---|---|
| **100nF** | C_DISC | 1 | C1 |
| **10uF** | C_ELEC | 1 | C2 |
| **74HCT04** | DIP14 | 1 | U1 |
| **PWR** | HDR2 | 1 | JP |
| **TCT40-16T** | HDR2 | 3 | T1 T2 T3 |
| **ESP32** | HDR4 | 1 | J1 |
| **100R** | R_AXIAL | 3 | R1 R2 R3 |

รวม 11 ชิ้น

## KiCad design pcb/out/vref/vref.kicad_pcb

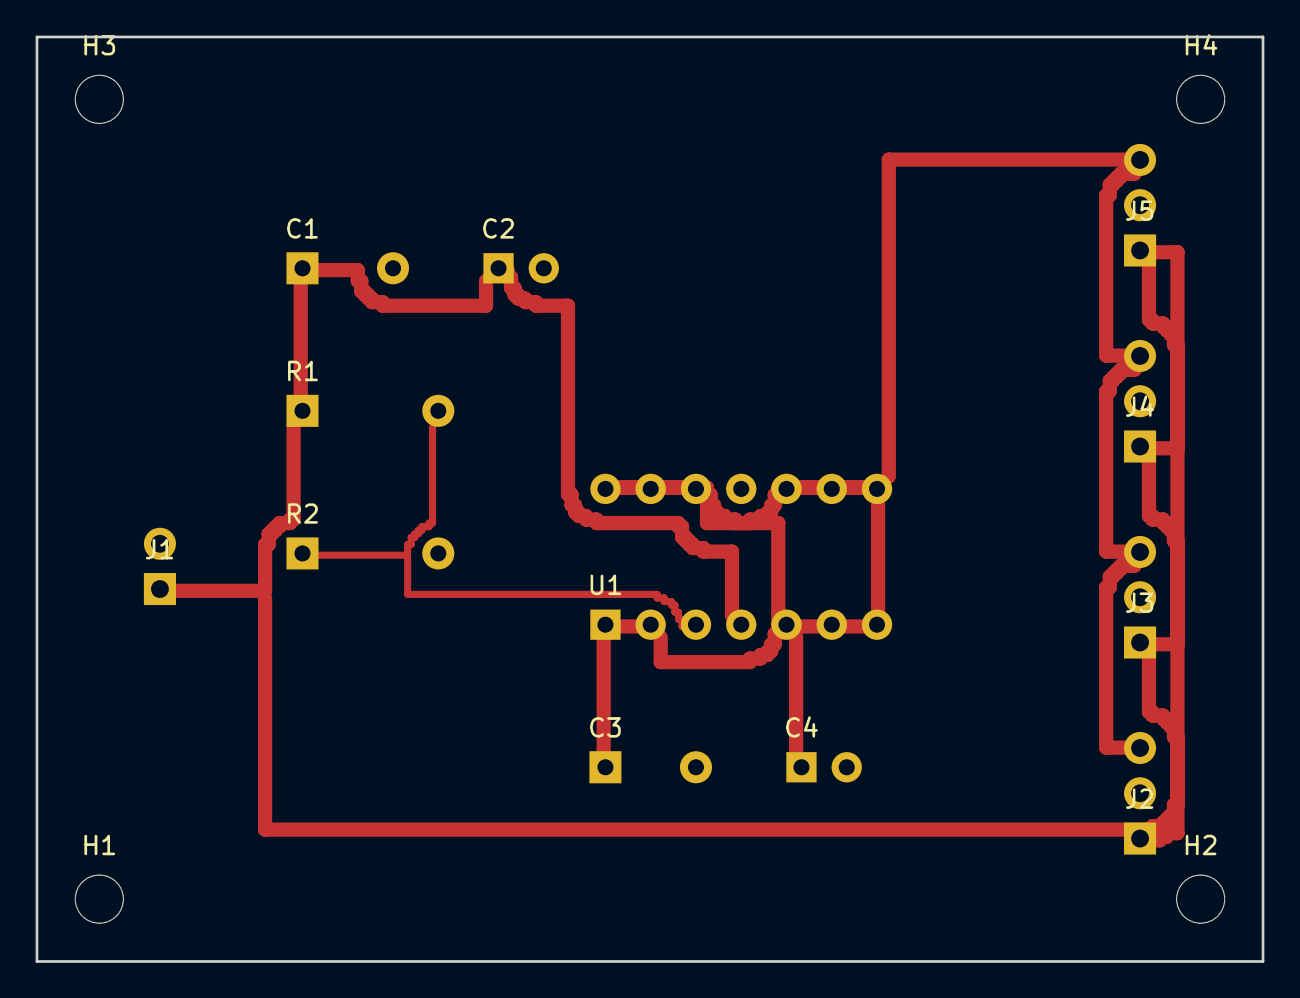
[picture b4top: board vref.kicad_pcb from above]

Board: 2 copper layers, 68.8 x 51.9 mm, 16 parts (0 on the bottom side), 4 nets.

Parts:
C1, C3: 100nF; C_DISC
C2, C4: 10uF; C_ELEC
H1, H2, H3, H4: M2.5; MountingHole
J1: 3V3 IN; HDR2
J2: OUT A; HDR3
J3: OUT B; HDR3
J4: OUT C; HDR3
J5: OUT D; HDR3
R1, R2: 10k; R_AXIAL
U1: MCP6004; DIP14

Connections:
3V3: C1.1, C2.1, J1.1, J2.1, J3.1, J4.1, J5.1, R1.1, U1.4
GND: C1.2, C2.2, C3.2, C4.2, J1.2, J2.2, J3.2, J4.2, J5.2, R2.2, U1.11
MID: R1.2, R2.1, U1.3
VREF: C3.1, C4.1, J2.3, J3.3, J4.3, J5.3, U1.1, U1.2, U1.5, U1.6, U1.7, U1.8, U1.9, U1.10, U1.12, U1.13, U1.14

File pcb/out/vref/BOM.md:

# vref — รายการชิ้นส่วน



| ค่า | ตัวถัง | จำนวน | อ้างอิง |
|---|---|---|---|
| **100nF** | C_DISC | 2 | C1 C3 |
| **10uF** | C_ELEC | 2 | C2 C4 |
| **MCP6004** | DIP14 | 1 | U1 |
| **3V3 IN** | HDR2 | 1 | J1 |
| **OUT A** | HDR3 | 1 | J2 |
| **OUT B** | HDR3 | 1 | J3 |
| **OUT C** | HDR3 | 1 | J4 |
| **OUT D** | HDR3 | 1 | J5 |
| **10k** | R_AXIAL | 2 | R1 R2 |

รวม 12 ชิ้น
